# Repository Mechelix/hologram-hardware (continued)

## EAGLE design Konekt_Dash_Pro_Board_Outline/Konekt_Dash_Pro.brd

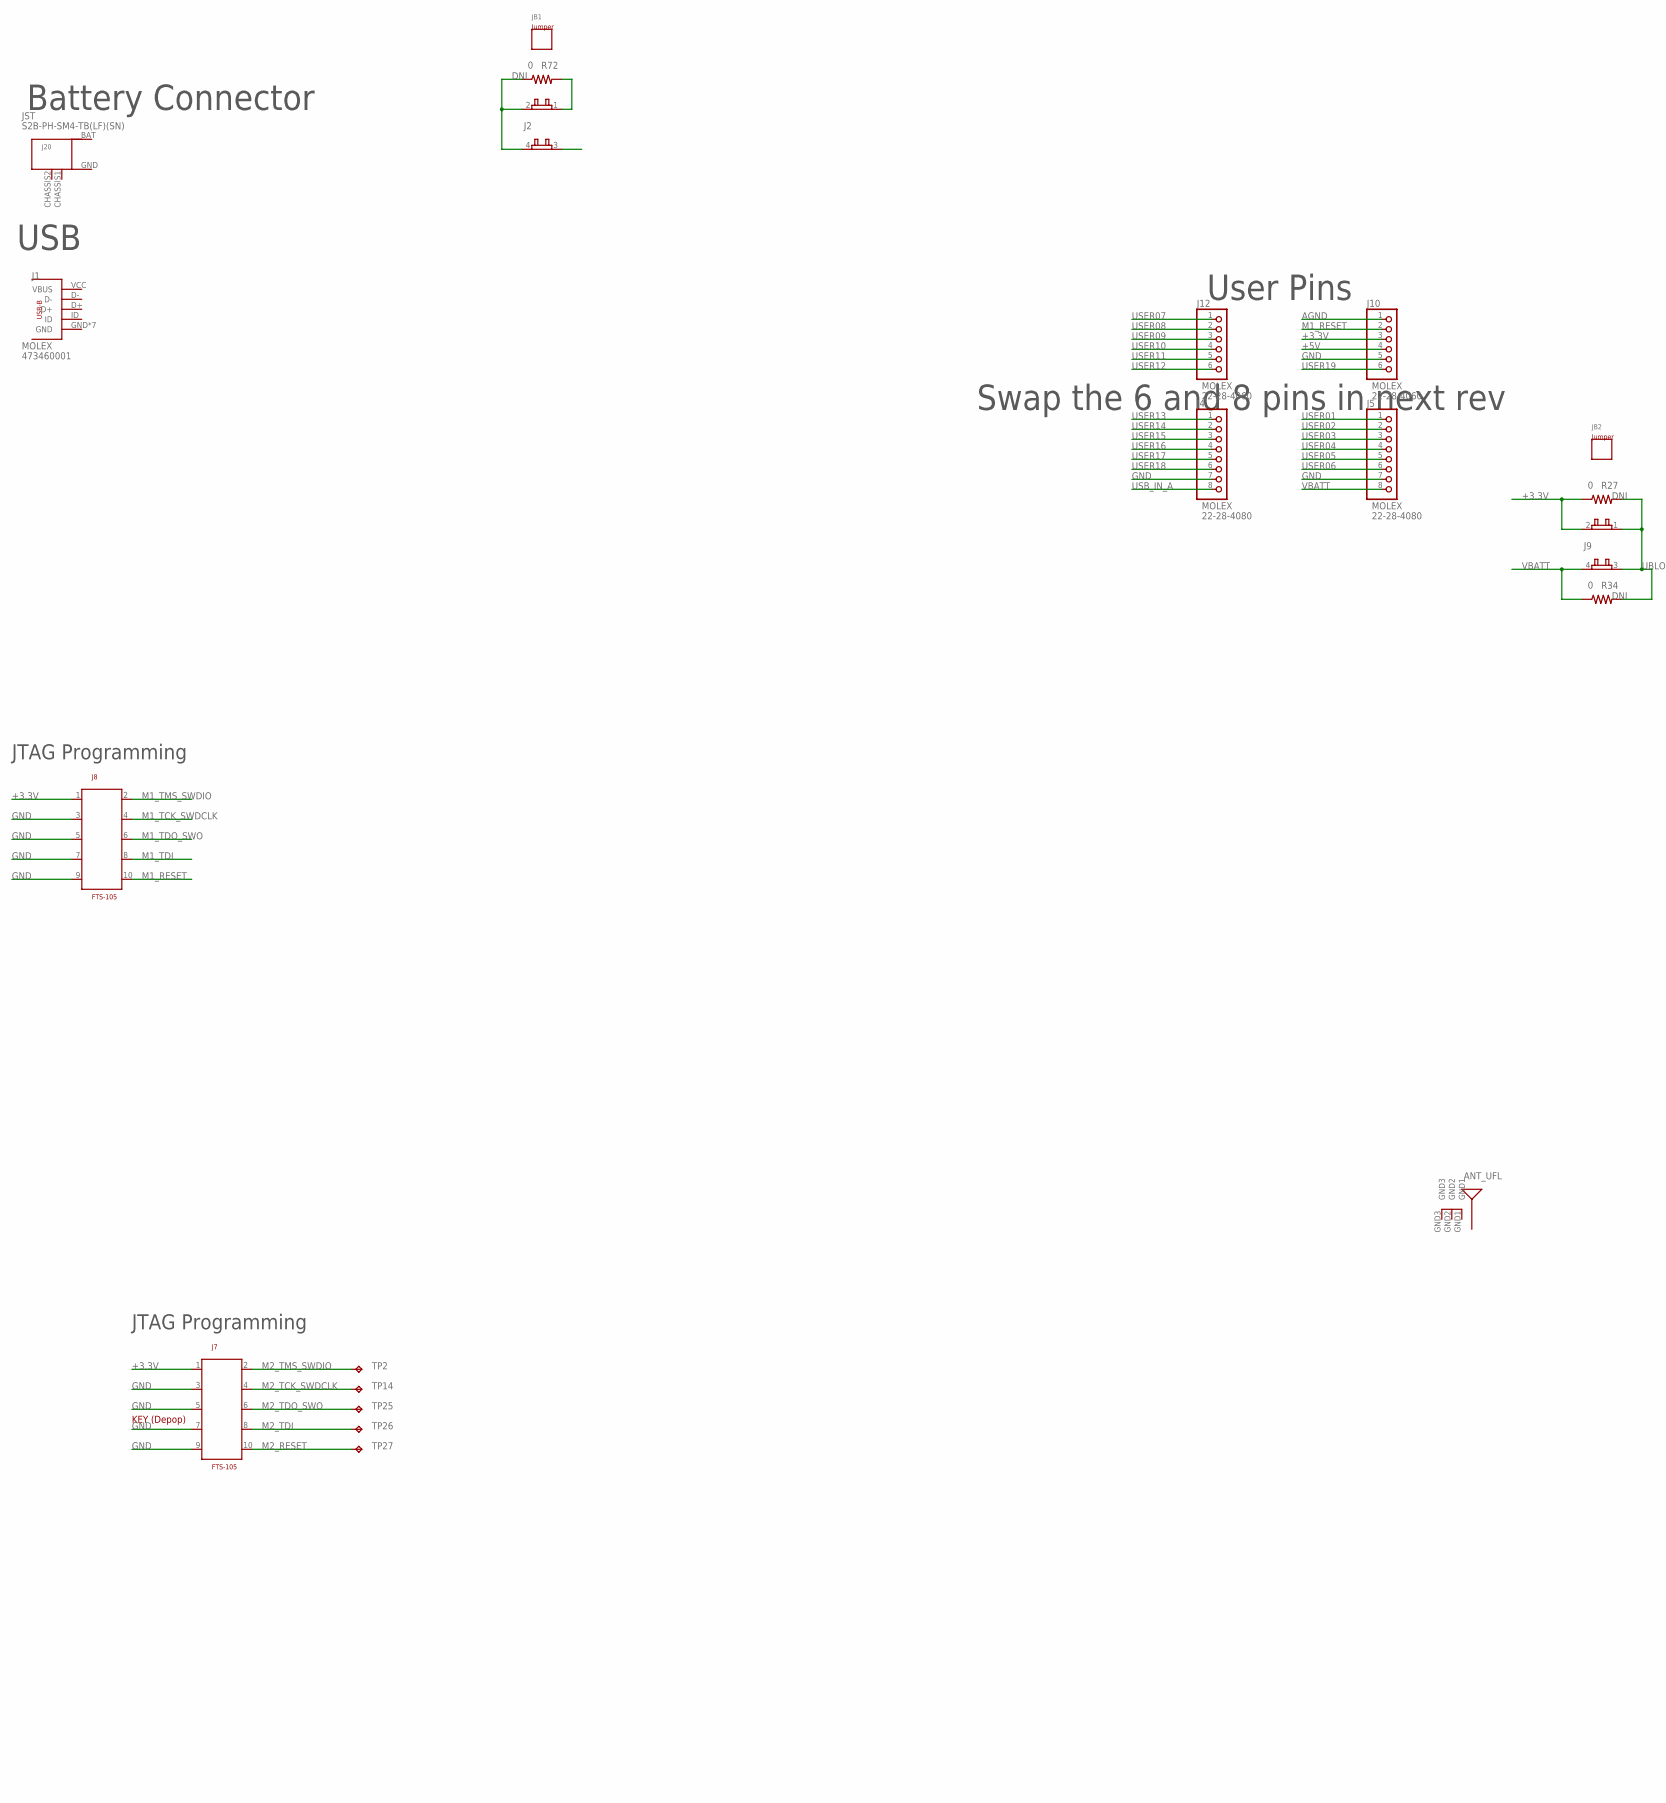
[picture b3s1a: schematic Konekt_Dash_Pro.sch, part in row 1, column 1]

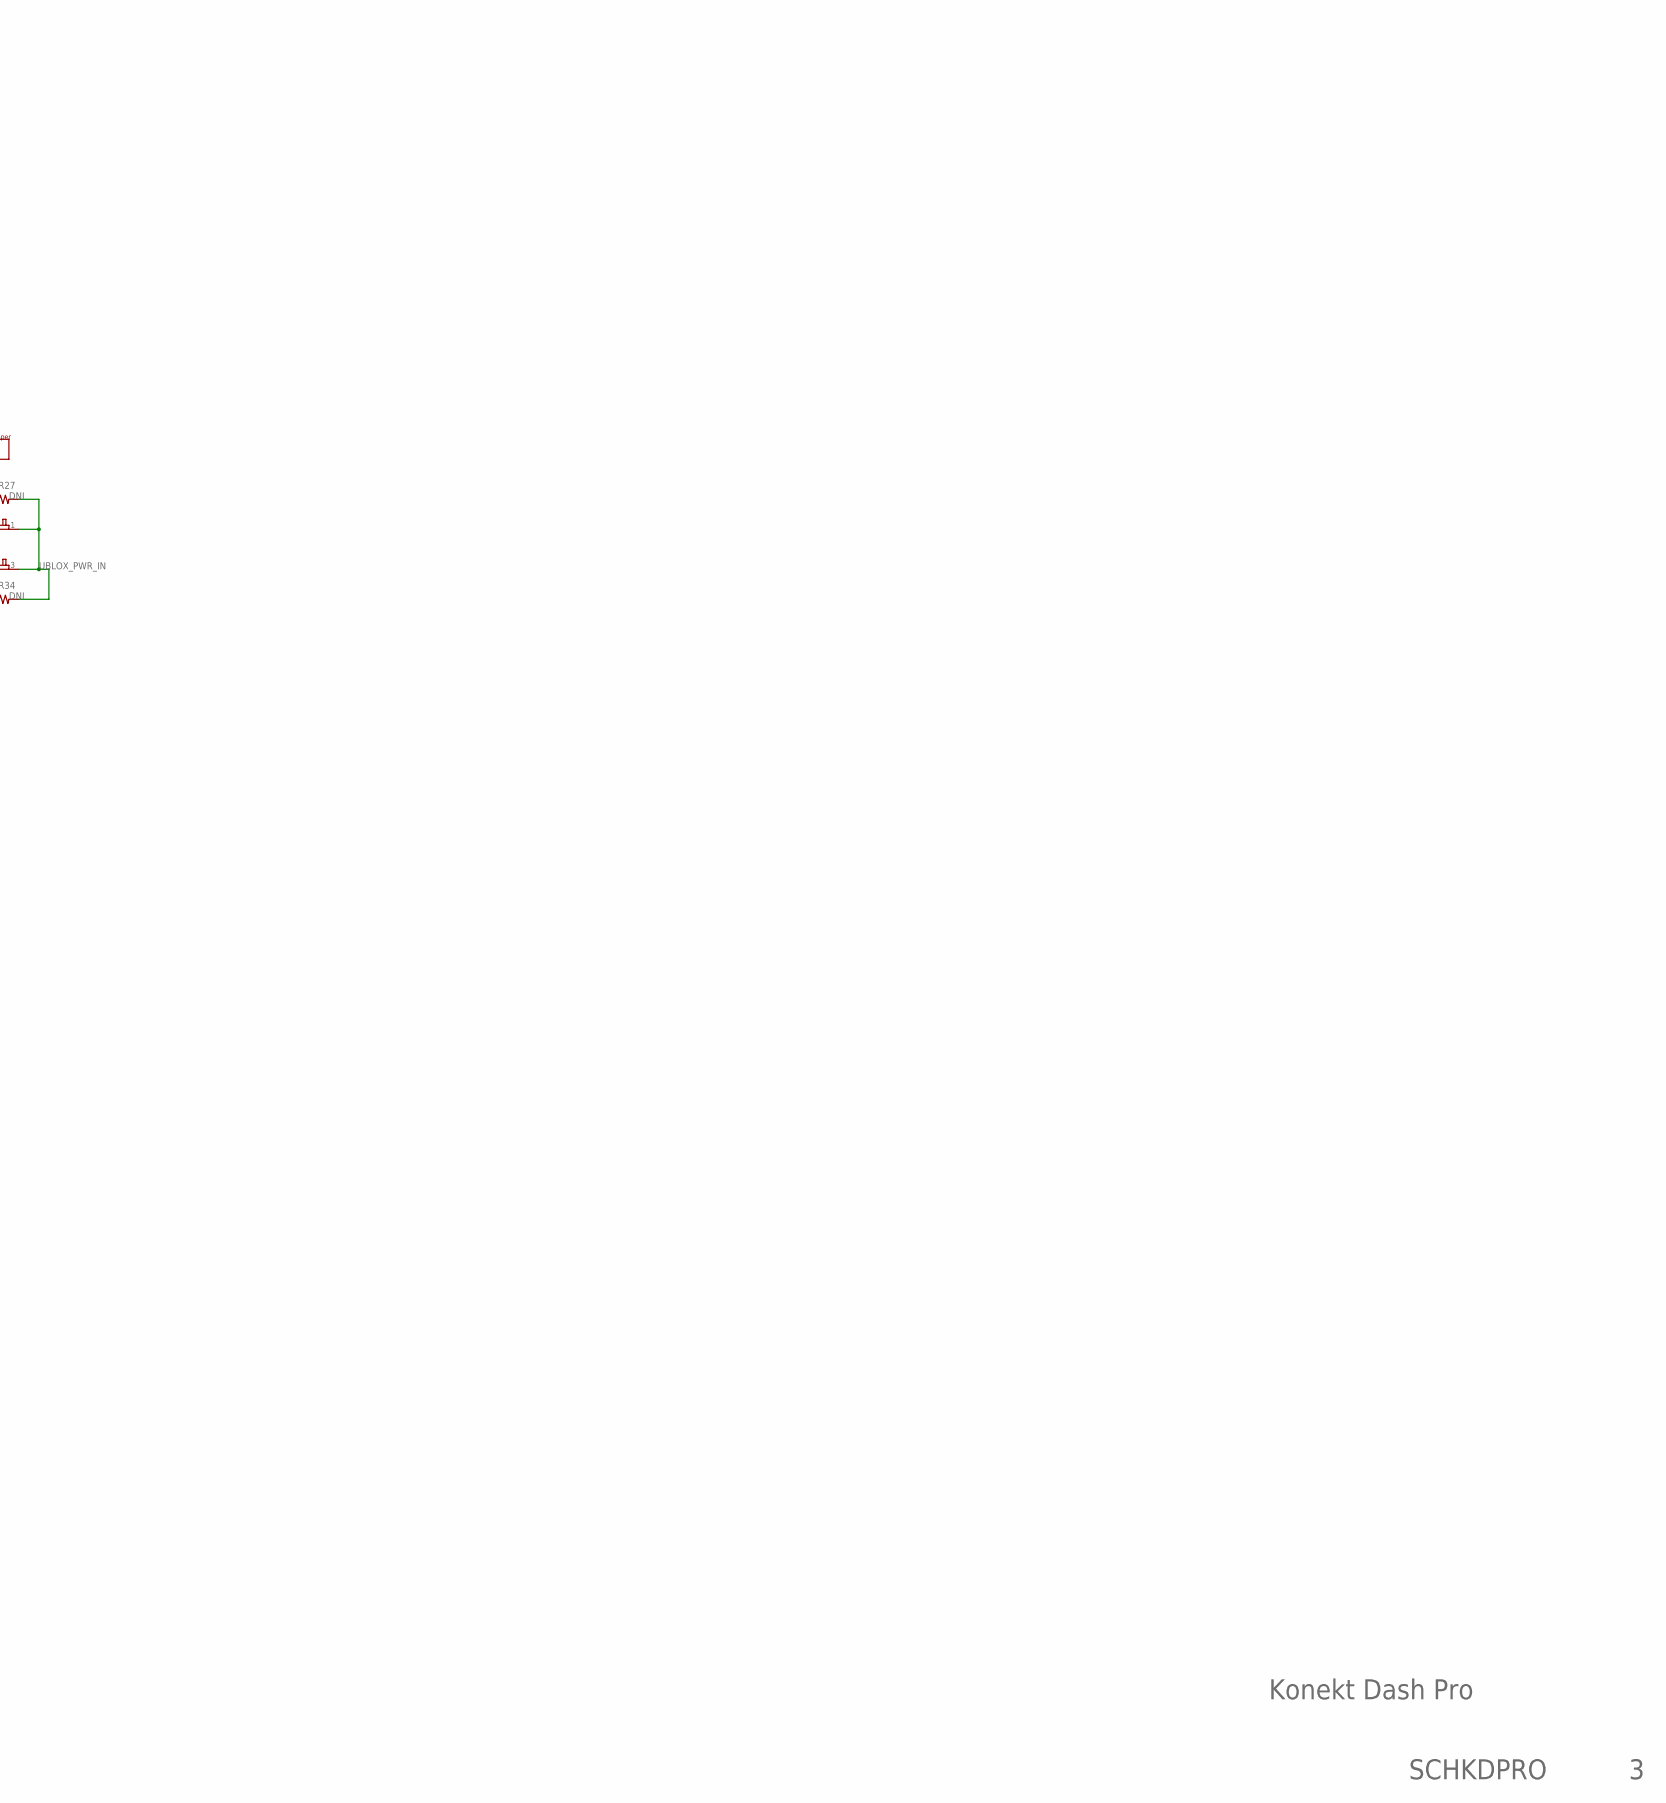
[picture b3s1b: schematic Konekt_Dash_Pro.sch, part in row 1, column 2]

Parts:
ANT_UFL: ANT-A-1JB; UFL; MPN A-1JB
J1: USB_MICRO_B_MOLEX_473460001; USB_MICRO_MOLEX_473460001; MPN 473460001
J2, J9: CON_JUMPER_1.27_2X2; FCI_CON_1.27_2X2
J4, J5: HEADER_0.1_IN_8_POS; HEADER_0.1_8_POS; MPN 22-28-4080
J7, J8: FTS-105; MPN DNI
J10, J12: PINHD-1X6; 1X06; MPN 22-28-4060
J20: BAT_TERM; JST-PH-2; MPN S2B-PH-SM4-TB(LF)(SN)
JB1, JB2: JUMPER_1.27MM; NOTHING
R27, R34, R72: 0; 0402-RES; MPN DNI
TP2, TP14, TP25, TP26, TP27: TPTP08R; TP08R; MPN N/A

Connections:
+3.3V: J7.1, J8.1, J9.2, J10.3, R27.1
+5V: J10.4
AGND: J10.1
GND: J4.7, J5.7, J7.3, J7.5, J7.7, J7.9, J8.3, J8.5, J8.7, J8.9, J10.5
M1_RESET: J8.10, J10.2
M1_TCK_SWDCLK: J8.4
M1_TDI: J8.8
M1_TDO_SWO: J8.6
M1_TMS_SWDIO: J8.2
M2_RESET: J7.10, TP27.TP
M2_TCK_SWDCLK: J7.4, TP14.TP
M2_TDI: J7.8, TP26.TP
M2_TDO_SWO: J7.6, TP25.TP
M2_TMS_SWDIO: J7.2, TP2.TP
unnamed: J2.1, R72.2
UBLOX_PWR_IN: J9.1, J9.3, R27.2, R34.2
USB_IN: J2.2, J2.4, R72.1
USB_IN_A: J4.8
USER01: J5.1
USER02: J5.2
USER03: J5.3
USER04: J5.4
USER05: J5.5
USER06: J5.6
USER07: J12.1
USER08: J12.2
USER09: J12.3
USER10: J12.4
USER11: J12.5
USER12: J12.6
USER13: J4.1
USER14: J4.2
USER15: J4.3
USER16: J4.4
USER17: J4.5
USER18: J4.6
USER19: J10.6
VBATT: J5.8, J9.4, R34.1

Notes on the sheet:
User Pins
Battery Connector
USB
JTAG Programming
KEY (Depop)
Konekt Dash Pro
SCHKDPRO
Swap the 6 and 8 pins in next rev

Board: 6 copper layers, 21 parts (10 on the bottom side), 12 nets, no tracks yet.

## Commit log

2016-01-04 updated board files to latest
2016-10-29 Update README links to latest URLs
